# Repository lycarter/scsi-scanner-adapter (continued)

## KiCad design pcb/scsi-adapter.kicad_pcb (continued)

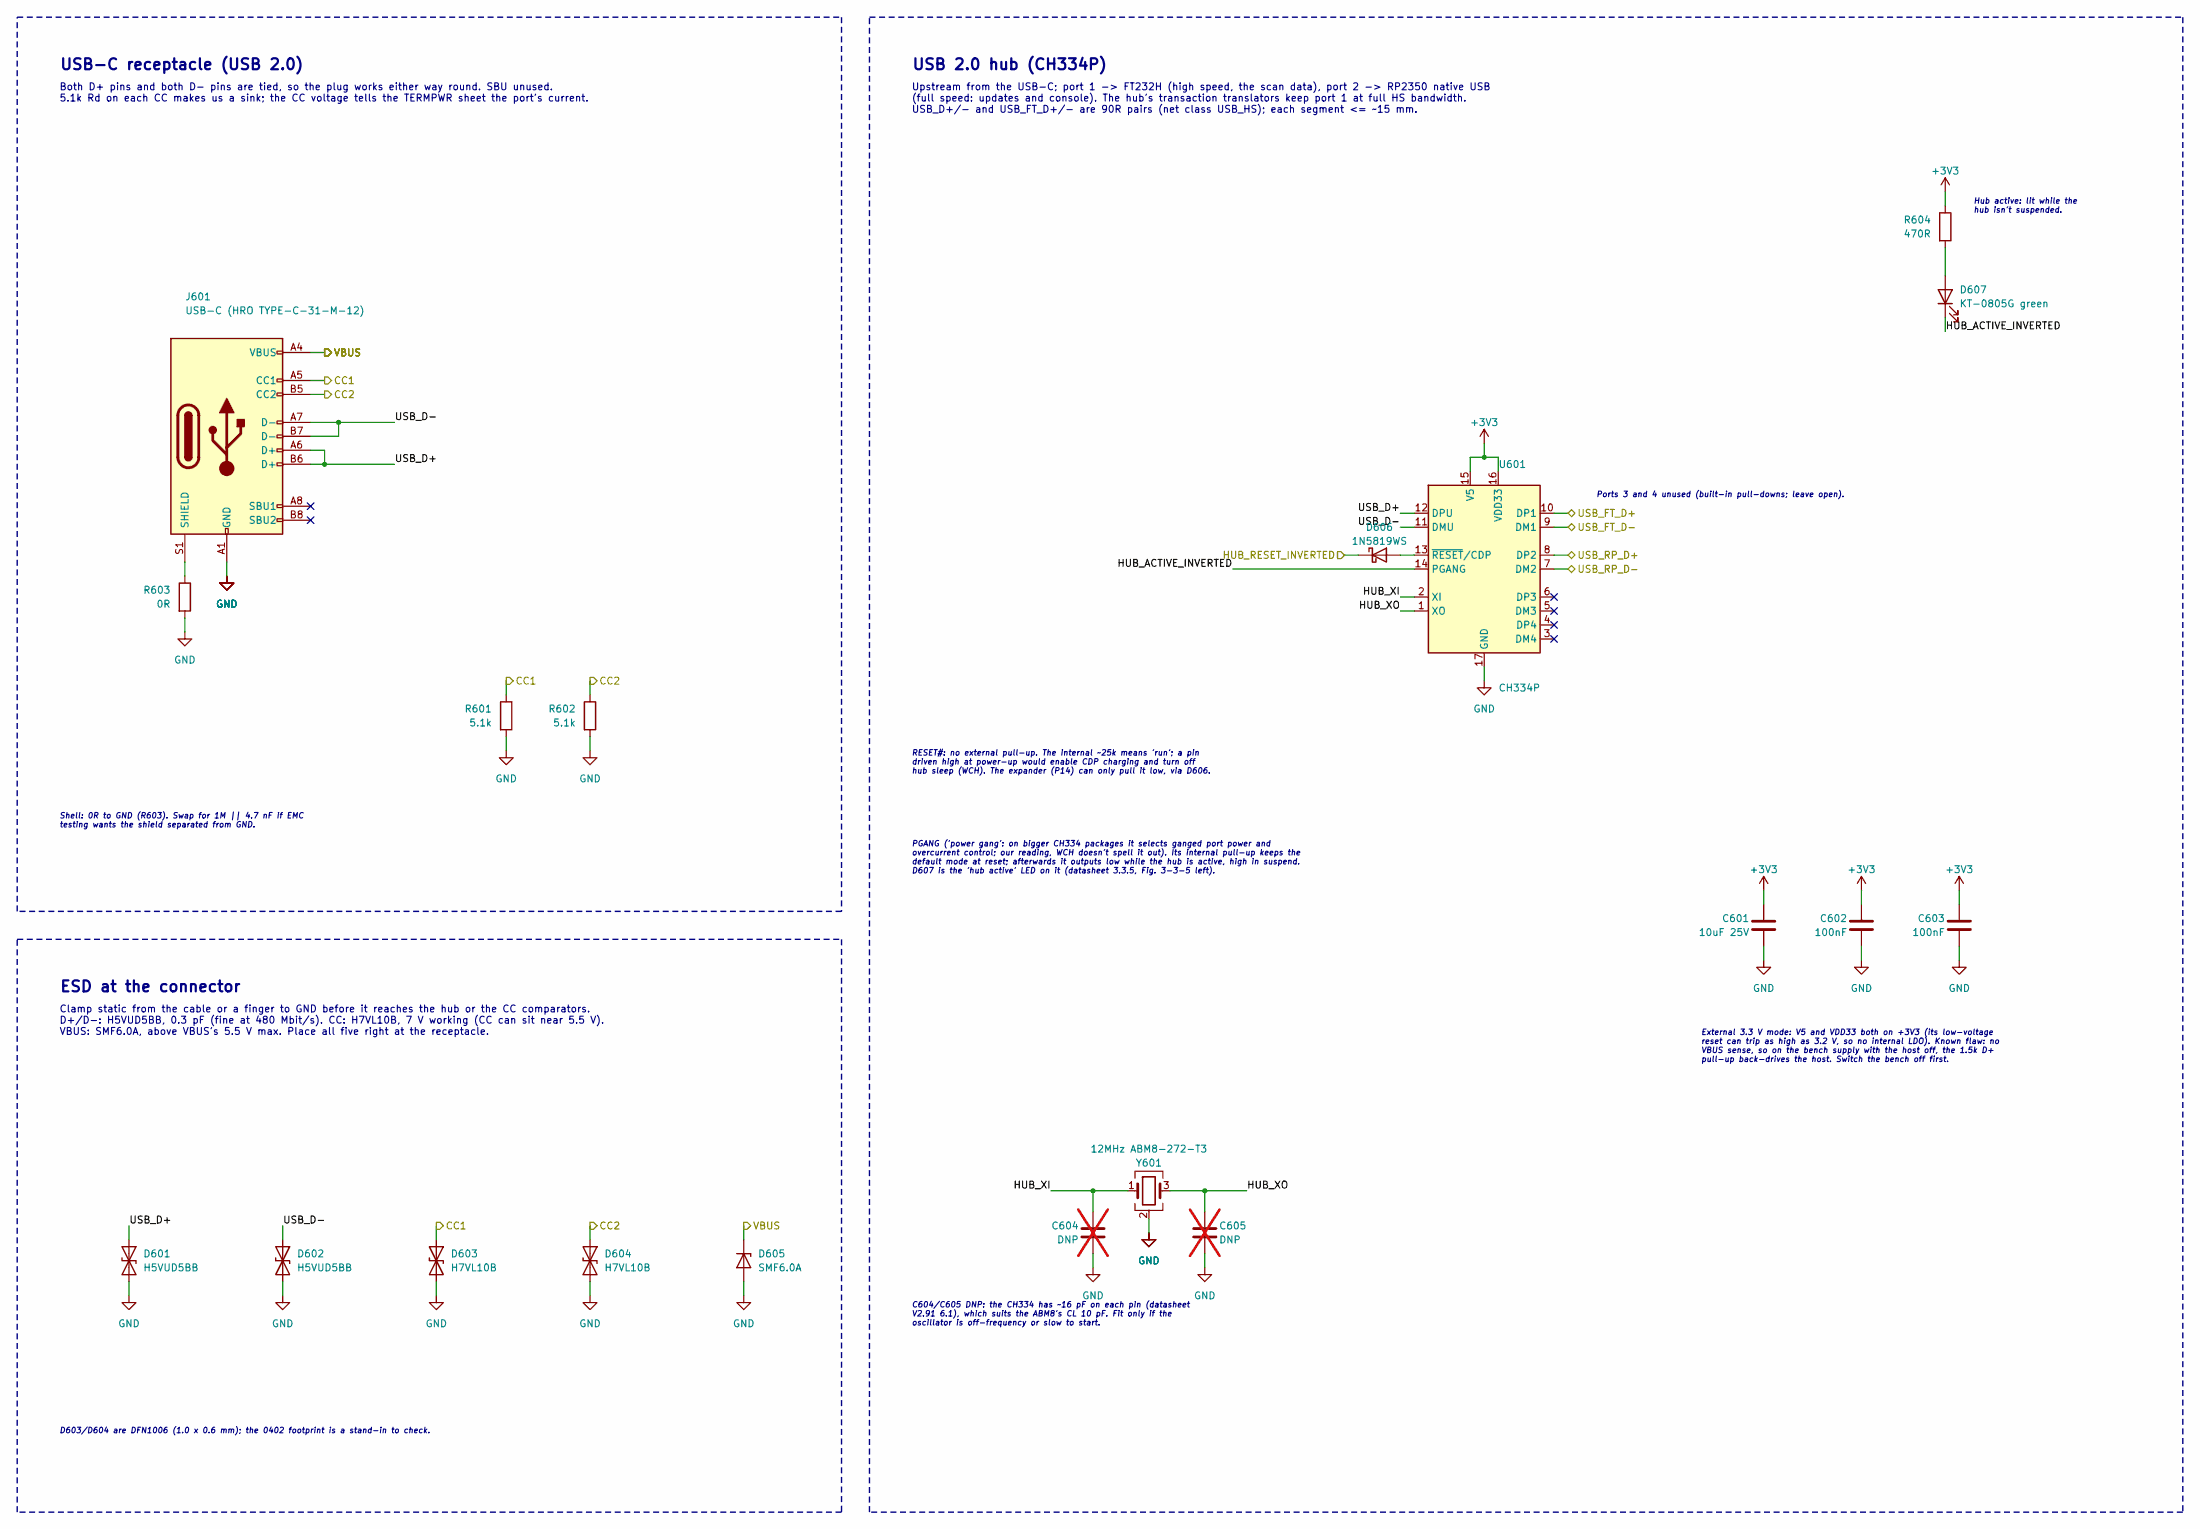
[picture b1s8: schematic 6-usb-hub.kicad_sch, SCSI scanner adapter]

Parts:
C601: 10uF 25V; C_0805_2012Metric; LCSC C15850
C602, C603: 100nF; C_0402_1005Metric; LCSC C307331
C604, C605: DNP; C_0402_1005Metric; not fitted
D601, D602: H5VUD5BB; D_SOD-523; LCSC C20615820
D603, D604: H7VL10B; D_0402_1005Metric; LCSC C20615787
D605: SMF6.0A; D_SOD-123F; LCSC C19077499
D606: 1N5819WS; D_SOD-323; LCSC C191023
D607: KT-0805G green; LED_0805_2012Metric; LCSC C2297
J601: USB-C (HRO TYPE-C-31-M-12); USB_C_Receptacle_HRO_TYPE-C-31-M-12
R601, R602: 5.1k; R_0402_1005Metric; LCSC C25905
R603: 0R; R_0402_1005Metric; LCSC C17168
R604: 470R; R_0402_1005Metric; LCSC C25117
U601: CH334P; QFN-16-1EP_3x3mm_P0.5mm_EP1.75x1.75mm; LCSC C5373042
Y601: 12MHz ABM8-272-T3; Crystal_SMD_3225-4Pin_3.2x2.5mm; LCSC C20625731

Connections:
+3V3: C601.1, C602.1, C603.1, R604.1, U601.15 (V5), U601.16 (VDD33); also elsewhere on the board
/CC1: D603.1 (A1), J601.A5 (CC1), R601.1; also elsewhere on the board
/CC2: D604.1 (A1), J601.B5 (CC2), R602.1; also elsewhere on the board
/HUB_RESET_INVERTED: D606.1 (K); also elsewhere on the board
/USB_FT_D+: U601.10 (DP1); also elsewhere on the board
/USB_FT_D-: U601.9 (DM1); also elsewhere on the board
/USB_RP_D+: U601.8 (DP2); also elsewhere on the board
/USB_RP_D-: U601.7 (DM2); also elsewhere on the board
/VBUS: D605.1 (K), J601.A4 (VBUS), J601.A9 (VBUS), J601.B4 (VBUS), J601.B9 (VBUS); also elsewhere on the board
/usb-hub/HUB_ACTIVE_INVERTED: D607.1 (K), U601.14 (PGANG)
/usb-hub/HUB_XI: C604.1, U601.2 (XI), Y601.1
/usb-hub/HUB_XO: C605.1, U601.1 (XO), Y601.3
/usb-hub/USB_D+: D601.1 (A1), J601.A6 (D+), J601.B6 (D+), U601.12 (DPU)
/usb-hub/USB_D-: D602.1 (A1), J601.A7 (D-), J601.B7 (D-), U601.11 (DMU)
GND: C601.2, C602.2, C603.2, C604.2, C605.2, D601.2 (A2), D602.2 (A2), D603.2 (A2), D604.2 (A2), D605.2 (A), J601.A1 (GND), J601.A12 (GND), J601.B1 (GND), J601.B12 (GND), R601.2, R602.2, R603.2, U601.17 (GND), Y601.2 (G), Y601.4 (G); also elsewhere on the board
unnamed: D606.2 (A), U601.13 (~RESET/CDP)
unnamed: D607.2 (A), R604.2
unnamed: J601.S1 (SHIELD), R603.1

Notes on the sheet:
PGANG ('power gang': on bigger CH334 packages it selects ganged port power and overcurrent control; our reading, WCH doesn't spell it out). Its internal pull-up keeps the default mode at reset; afterwards it outputs low while the hub is active, high in suspend. D607 is the 'hub active' LED on it (d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
C604/C605 DNP: the CH334 has ~16 pF on each pin (datasheet V2.91 6.1), which suits the ABM8's CL 10 pF. Fit only if the oscillator is off-frequency or slow to start.
RESET#: no external pull-up. The internal ~25k means 'run'; a pin driven high at power-up would enable CDP charging and turn off hub sleep (WCH). The expander (P14) can only pull it low, via D606.
ESD at the connector
Clamp static from the cable or a finger to GND before it reaches the hub or the CC comparators. D+/D-: H5VUD5BB, 0.3 pF (fine at 480 Mbit/s). CC: H7VL10B, 7 V working (CC can sit near 5.5 V). VBUS: SMF6.0A, above VBUS's 5.5 V max. Place all five right at the receptacle.
Shell: 0R to GND (R603). Swap for 1M || 4.7 nF if EMC testing wants the shield separated from GND.
External 3.3 V mode: V5 and VDD33 both on +3V3 (its low-voltage reset can trip as high as 3.2 V, so no internal LDO). Known flaw: no VBUS sense, so on the bench supply with the host off, the 1.5k D+ pull-up back-drives the host. Switch the bench off first.
Upstream from the USB-C; port 1 -> FT232H (high speed, the scan data), port 2 -> RP2350 native USB (full speed: updates and console). The hub's transaction translators keep port 1 at full HS bandwidth. USB_D+/- and USB_FT_D+/- are 90R pairs (net class USB_HS); each segment <= ~15 mm.
USB-C receptacle (USB 2.0)
Both D+ pins and both D- pins are tied, so the plug works either way round. SBU unused. 5.1k Rd on each CC makes us a sink; the CC voltage tells the TERMPWR sheet the port's current.
D603/D604 are DFN1006 (1.0 x 0.6 mm); the 0402 footprint is a stand-in to check.
USB 2.0 hub (CH334P)
Hub active: lit while the hub isn't suspended.
Ports 3 and 4 unused (built-in pull-downs; leave open).

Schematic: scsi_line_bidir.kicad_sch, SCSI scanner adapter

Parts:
C901: 22pF C0G; C_0402_1005Metric; LCSC C1555; not fitted
C902: 100nF 50V; C_0402_1005Metric; LCSC C307331
Q901: FDV301N; SOT-23; LCSC C15310
R901, R903: 100R; R_0402_1005Metric; LCSC C25076
R902: 4.7k; R_0402_1005Metric; LCSC C25900
U901: 74LVC1G17GW; SOT-353_SC-70-5; LCSC C426705

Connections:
+3V3: C902.1, U901.5 (VCC); also elsewhere on the board
/DB0_GATE: R901.1; also elsewhere on the board
/DB0_RX: R903.1, U901.4; also elsewhere on the board
/scsi/DB0_LOGIC_ANALYZER: R903.2; also elsewhere on the board
/scsi/~DB0: Q901.3 (D), U901.2; also elsewhere on the board
GND: C901.2, C902.2, Q901.2 (S), R902.2, U901.3 (GND); also elsewhere on the board
unnamed: C901.1, Q901.1 (G), R901.2, R902.1

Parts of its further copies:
C1001, C1101, C1201, C1301, C1401, C1501, C1601, C1701, C1801, C1901, C2001, C2101, C2301: 22pF C0G; C_0402_1005Metric; LCSC C1555; not fitted
C1002, C1102, C1202, C1302, C1402, C1502, C1602, C1702, C1802, C1902, C2002, C2102, C2302: 100nF 50V; C_0402_1005Metric; LCSC C307331
Q1001, Q1101, Q1201, Q1301, Q1401, Q1501, Q1601, Q1701, Q1801, Q1901, Q2001, Q2101, Q2301: FDV301N; SOT-23; LCSC C15310
R1001, R1003, R1101, R1103, R1201, R1203, R1301, R1303, R1401, R1403, R1501, R1503, R1601, R1603, R1701, R1703, R1801, R1803, R1901, R1903, R2001, R2003, R2101, R2103, R2301, R2303: 100R; R_0402_1005Metric; LCSC C25076
R1002, R1102, R1202, R1302, R1402, R1502, R1602, R1702, R1802, R1902, R2002, R2102, R2302: 4.7k; R_0402_1005Metric; LCSC C25900
U1001, U1101, U1201, U1301, U1401, U1501, U1601, U1701, U1801, U1901, U2001, U2101, U2301: 74LVC1G17GW; SOT-353_SC-70-5; LCSC C426705

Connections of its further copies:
+3V3: C1002.1, C1102.1, C1202.1, C1302.1, C1402.1, C1502.1, C1602.1, C1702.1, C1802.1, C1902.1, C2002.1, C2102.1, C2302.1, U1001.5 (VCC), U1101.5 (VCC), U1201.5 (VCC), U1301.5 (VCC), U1401.5 (VCC), U1501.5 (VCC), U1601.5 (VCC), U1701.5 (VCC), U1801.5 (VCC), U1901.5 (VCC), U2001.5 (VCC), U2101.5 (VCC), U2301.5 (VCC); also elsewhere on the board
/ACK_GATE: R2001.1; also elsewhere on the board
/ACK_RX: R2003.1, U2001.4; also elsewhere on the board
/ATN_GATE: R1801.1; also elsewhere on the board
/ATN_RX: R1803.1, U1801.4; also elsewhere on the board
/BSY_GATE: R1901.1; also elsewhere on the board
/BSY_RX: R1903.1, U1901.4; also elsewhere on the board
/DB1_GATE: R1001.1; also elsewhere on the board
/DB1_RX: R1003.1, U1001.4; also elsewhere on the board
/DB2_GATE: R1101.1; also elsewhere on the board
/DB2_RX: R1103.1, U1101.4; also elsewhere on the board
/DB3_GATE: R1201.1; also elsewhere on the board
/DB3_RX: R1203.1, U1201.4; also elsewhere on the board
/DB4_GATE: R1301.1; also elsewhere on the board
/DB4_RX: R1303.1, U1301.4; also elsewhere on the board
/DB5_GATE: R1401.1; also elsewhere on the board
/DB5_RX: R1403.1, U1401.4; also elsewhere on the board
/DB6_GATE: R1501.1; also elsewhere on the board
/DB6_RX: R1503.1, U1501.4; also elsewhere on the board
/DB7_GATE: R1601.1; also elsewhere on the board
/DB7_RX: R1603.1, U1601.4; also elsewhere on the board
/DBP_GATE: R1701.1; also elsewhere on the board
/DBP_RX: R1703.1, U1701.4; also elsewhere on the board
/RST_GATE: R2101.1; also elsewhere on the board
/RST_RX: R2103.1, U2101.4; also elsewhere on the board
/SEL_GATE: R2301.1; also elsewhere on the board
/SEL_RX: R2303.1, U2301.4; also elsewhere on the board
/scsi/ACK_LOGIC_ANALYZER: R2003.2; also elsewhere on the board
/scsi/ATN_LOGIC_ANALYZER: R1803.2; also elsewhere on the board
/scsi/BSY_LOGIC_ANALYZER: R1903.2; also elsewhere on the board
/scsi/DB1_LOGIC_ANALYZER: R1003.2; also elsewhere on the board
/scsi/DB2_LOGIC_ANALYZER: R1103.2; also elsewhere on the board
/scsi/DB3_LOGIC_ANALYZER: R1203.2; also elsewhere on the board
/scsi/DB4_LOGIC_ANALYZER: R1303.2; also elsewhere on the board
/scsi/DB5_LOGIC_ANALYZER: R1403.2; also elsewhere on the board
/scsi/DB6_LOGIC_ANALYZER: R1503.2; also elsewhere on the board
/scsi/DB7_LOGIC_ANALYZER: R1603.2; also elsewhere on the board
/scsi/DBP_LOGIC_ANALYZER: R1703.2; also elsewhere on the board
/scsi/RST_LOGIC_ANALYZER: R2103.2; also elsewhere on the board
/scsi/SEL_LOGIC_ANALYZER: R2303.2; also elsewhere on the board
/scsi/~ACK: Q2001.3 (D), U2001.2; also elsewhere on the board
/scsi/~ATN: Q1801.3 (D), U1801.2; also elsewhere on the board
/scsi/~BSY: Q1901.3 (D), U1901.2; also elsewhere on the board
/scsi/~DB1: Q1001.3 (D), U1001.2; also elsewhere on the board
/scsi/~DB2: Q1101.3 (D), U1101.2; also elsewhere on the board
/scsi/~DB3: Q1201.3 (D), U1201.2; also elsewhere on the board
/scsi/~DB4: Q1301.3 (D), U1301.2; also elsewhere on the board
/scsi/~DB5: Q1401.3 (D), U1401.2; also elsewhere on the board
/scsi/~DB6: Q1501.3 (D), U1501.2; also elsewhere on the board
/scsi/~DB7: Q1601.3 (D), U1601.2; also elsewhere on the board
/scsi/~DBP: Q1701.3 (D), U1701.2; also elsewhere on the board
/scsi/~RST: Q2101.3 (D), U2101.2; also elsewhere on the board
/scsi/~SEL: Q2301.3 (D), U2301.2; also elsewhere on the board
GND: C1001.2, C1002.2, C1101.2, C1102.2, C1201.2, C1202.2, C1301.2, C1302.2, C1401.2, C1402.2, C1501.2, C1502.2, C1601.2, C1602.2, C1701.2, C1702.2, C1801.2, C1802.2, C1901.2, C1902.2, C2001.2, C2002.2, C2101.2, C2102.2, C2301.2, C2302.2, Q1001.2 (S), Q1101.2 (S), Q1201.2 (S), Q1301.2 (S), Q1401.2 (S), Q1501.2 (S), Q1601.2 (S), Q1701.2 (S), Q1801.2 (S), Q1901.2 (S), Q2001.2 (S), Q2101.2 (S), Q2301.2 (S), R1002.2, R1102.2, R1202.2, R1302.2, R1402.2, R1502.2, R1602.2, R1702.2, R1802.2, R1902.2, R2002.2, R2102.2, R2302.2, U1001.3 (GND), U1101.3 (GND), U1201.3 (GND), U1301.3 (GND), U1401.3 (GND), U1501.3 (GND), U1601.3 (GND), U1701.3 (GND), U1801.3 (GND), U1901.3 (GND), U2001.3 (GND), U2101.3 (GND), U2301.3 (GND); also elsewhere on the board
unnamed: C1001.1, Q1001.1 (G), R1001.2, R1002.1
unnamed: C1101.1, Q1101.1 (G), R1101.2, R1102.1
unnamed: C1201.1, Q1201.1 (G), R1201.2, R1202.1
unnamed: C1301.1, Q1301.1 (G), R1301.2, R1302.1
unnamed: C1401.1, Q1401.1 (G), R1401.2, R1402.1
unnamed: C1501.1, Q1501.1 (G), R1501.2, R1502.1
unnamed: C1601.1, Q1601.1 (G), R1601.2, R1602.1
unnamed: C1701.1, Q1701.1 (G), R1701.2, R1702.1
unnamed: C1801.1, Q1801.1 (G), R1801.2, R1802.1
unnamed: C1901.1, Q1901.1 (G), R1901.2, R1902.1
unnamed: C2001.1, Q2001.1 (G), R2001.2, R2002.1
unnamed: C2101.1, Q2101.1 (G), R2101.2, R2102.1
unnamed: C2301.1, Q2301.1 (G), R2301.2, R2302.1

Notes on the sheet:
SCSI line with driver
C1 DNP: fit only if a rising bus edge, coupled through the FET's gate-drain capacitance, makes a visible dip or step (board off, G4 driving the bus).
x14: DB0-7, DBP, ATN, BSY, ACK, RST, SEL (pages 9-21 except MSG). References: page x 100 + n. Driver: GATE high = line asserted (Q1 pulls it to ~0.2 V). Receiver: RX low = line asserted (the RP2350 pad inverts it). Place this cluster on its own bus trace next to the connector.
R3 feeds the logic-analyzer header; the RP2350 input takes RX straight from U1.

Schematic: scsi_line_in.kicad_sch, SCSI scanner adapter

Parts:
C2202: 100nF 50V; C_0402_1005Metric; LCSC C307331
R2203: 100R; R_0402_1005Metric; LCSC C25076
U2201: 74LVC1G17GW; SOT-353_SC-70-5; LCSC C426705

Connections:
+3V3: C2202.1, U2201.5 (VCC); also elsewhere on the board
/MSG_RX: R2203.1, U2201.4; also elsewhere on the board
/scsi/MSG_LOGIC_ANALYZER: R2203.2; also elsewhere on the board
/scsi/~MSG: U2201.2; also elsewhere on the board
GND: C2202.2, U2201.3 (GND); also elsewhere on the board

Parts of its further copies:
C2402, C2502, C2602: 100nF 50V; C_0402_1005Metric; LCSC C307331
R2403, R2503, R2603: 100R; R_0402_1005Metric; LCSC C25076
U2401, U2501, U2601: 74LVC1G17GW; SOT-353_SC-70-5; LCSC C426705

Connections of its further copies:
+3V3: C2402.1, C2502.1, C2602.1, U2401.5 (VCC), U2501.5 (VCC), U2601.5 (VCC); also elsewhere on the board
/CD_RX: R2403.1, U2401.4; also elsewhere on the board
/IO_RX: R2603.1, U2601.4; also elsewhere on the board
/REQ_RX: R2503.1, U2501.4; also elsewhere on the board
/scsi/CD_LOGIC_ANALYZER: R2403.2; also elsewhere on the board
/scsi/IO_LOGIC_ANALYZER: R2603.2; also elsewhere on the board
/scsi/REQ_LOGIC_ANALYZER: R2503.2; also elsewhere on the board
/scsi/~CD: U2401.2; also elsewhere on the board
/scsi/~IO: U2601.2; also elsewhere on the board
/scsi/~REQ: U2501.2; also elsewhere on the board
GND: C2402.2, C2502.2, C2602.2, U2401.3 (GND), U2501.3 (GND), U2601.3 (GND); also elsewhere on the board

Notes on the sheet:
x4: MSG, C/D, REQ, I/O. The initiator never drives these (SCSI-2 Table 6: target-only). RX low = line asserted (the RP2350 pad inverts it). References: page x 100 + n.
SCSI line, receive only
R3 feeds the logic-analyzer header; the RP2350 input takes RX straight from U1.

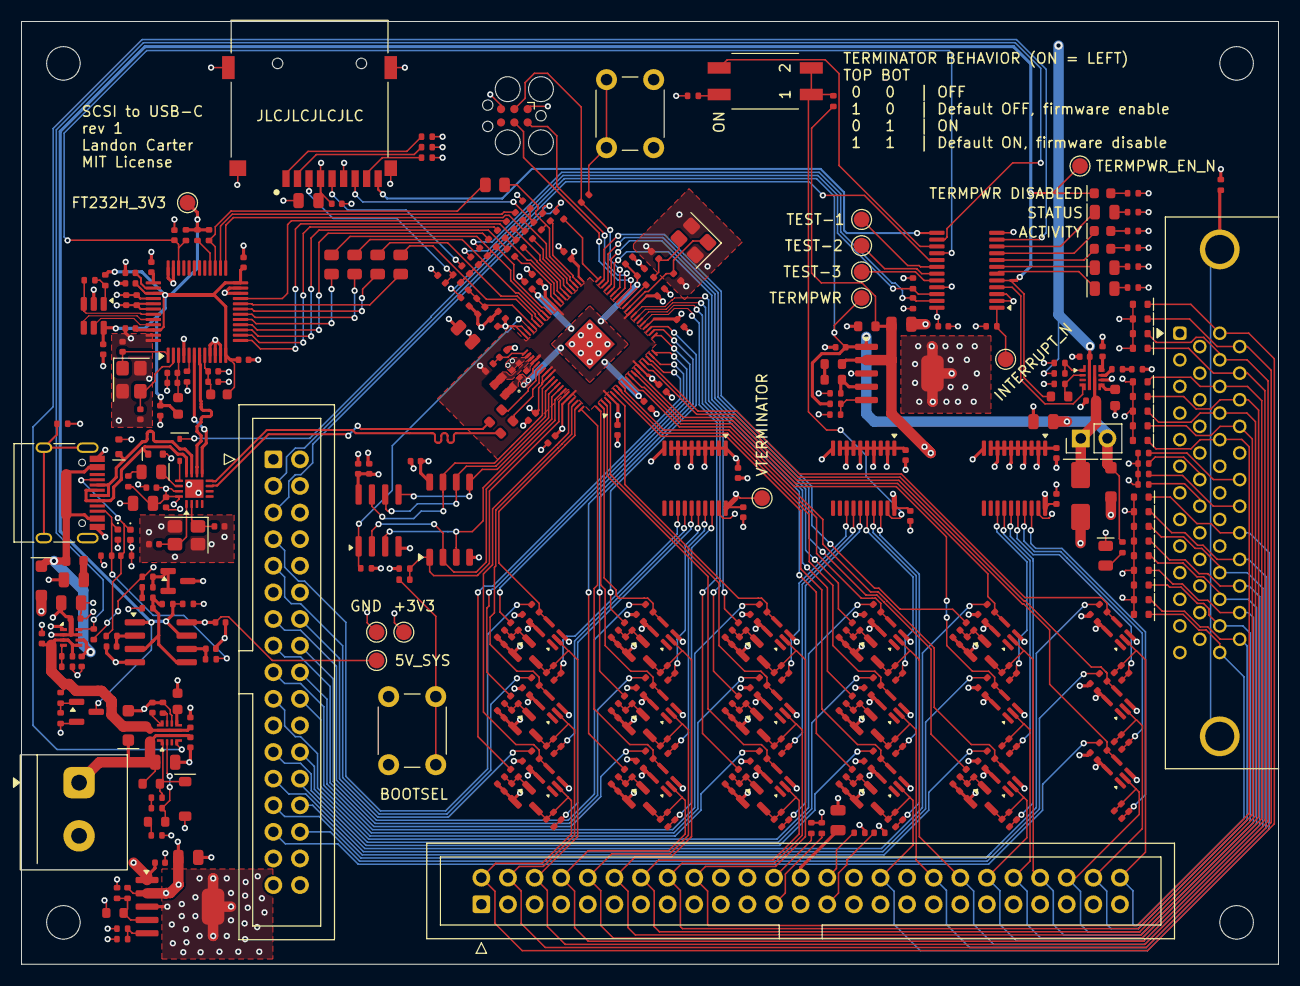
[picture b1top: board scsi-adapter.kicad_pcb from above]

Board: 4 copper layers, 120.0 x 90.0 mm, 412 parts (0 on the bottom side), 254 nets.

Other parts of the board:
5V_SYS: +5V_SYS; TestPoint_Pad_D1.5mm
+3V3: +3V3; TestPoint_Pad_D1.5mm
FT232H_3V3: FT232H_3V3; TestPoint_Pad_D1.5mm
GND: GND; TestPoint_Pad_D1.5mm
H1, H2, H3, H4: M3; MountingHole_3.2mm_M3
INTERRUPT_N: INT; TestPoint_Pad_D1.5mm
TERMPWR: TERMPWR; TestPoint_Pad_D1.5mm
TERMPWR_EN_N: TP_EN; TestPoint_Pad_D1.5mm
TEST-1: P15; TestPoint_Pad_D1.5mm
TEST-2: P16; TestPoint_Pad_D1.5mm
TEST-3: P17; TestPoint_Pad_D1.5mm
VTERMINATOR: VTERM; TestPoint_Pad_D1.5mm

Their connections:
+3V3: +3V3.1; also elsewhere on the board
+5V_SYS: 5V_SYS.1; also elsewhere on the board
/TERMPWR_EN_INVERTED: TERMPWR_EN_N.1; also elsewhere on the board
/io/EXPANDER_INTERRUPT_INVERTED: INTERRUPT_N.1; also elsewhere on the board
/io/EXPANDER_P15: TEST-1.1; also elsewhere on the board
/io/EXPANDER_P16: TEST-2.1; also elsewhere on the board
/io/EXPANDER_P17: TEST-3.1; also elsewhere on the board
FT232H_3V3: FT232H_3V3.1; also elsewhere on the board
GND: GND.1; also elsewhere on the board
TERMPWR: TERMPWR.1; also elsewhere on the board
VTERMINATOR: VTERMINATOR.1; also elsewhere on the board

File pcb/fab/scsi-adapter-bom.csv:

Comment,Designator,Footprint,LCSC Part #
1uF 50V X7R,C101,C_0805_2012Metric,C28323
100nF 50V,"C102,C108,C203,C206,C301,C302,C303,C304,C305,C306,C406,C407,C408,C409,C410,C411,C412,C413,C414,C415,C416,C417,C418,C421,C422,C424,C501,C503,C602,C603,C702,C704,C705,C706,C707,C708,C710,C712,C713,C714,C902,C1002,C1102,C1202,C1302,C1402,C1502,C1602,C1702,C1802,C1902,C2002,C2102,C2202,C2302,C2402,C2502,C2602",C_0402_1005Metric,C307331
2.2nF,"C103,C204",C_0603_1608Metric,C1604
1uF 25V,"C105,C106,C110,C112,C114,C201,C202,C207,C423",C_0402_1005Metric,C52923
4.7uF 25V,"C107,C307,C308",C_0805_2012Metric,C1779
22uF 25V,C109,C_0805_2012Metric,C45783
10uF 25V,"C111,C113,C405,C502,C601",C_0805_2012Metric,C15850
4.7uF 10V,"C401,C402,C403,C404,C701,C703",C_0402_1005Metric,C23733
15pF,"C419,C420,C715,C716",C_0402_1005Metric,C1548
10nF,C717,C_0402_1005Metric,C15195
BZT52C5V6,D102,D_SOD-123,C19077402
KT-0603R red,"D201,D502,D503",LED_0603_1608Metric,C2286
KT-0805Y yellow,"D202,D501,D504",LED_0805_2012Metric,C2296
SMF6.0A,"D204,D605",D_SOD-123F,C19077499
H5VUD5BB,"D301,D302,D303,D304,D305,D306,D307,D308,D309,D310,D311,D312,D313,D314,D315,D316,D317,D318,D601,D602",D_SOD-523,C20615820
KT-0805G green,"D505,D607",LED_0805_2012Metric,C2297
H7VL10B,"D603,D604",D_0402_1005Metric,C20615787
1N5819WS,D606,D_SOD-323,C191023
600R@100MHz,"FB701,FB702",L_0603_1608Metric,C1002
TF PUSH,J501,microSD_SHOUHAN_TF-PUSH_PushPush_CardDetect,C393941
3.3uH,L401,L_Abracon_AOTA-B201610_2.0x1.6mm_Polarized,C42411119
2N7002,Q201,SOT-23,C8545
FDV301N,"Q901,Q1001,Q1101,Q1201,Q1301,Q1401,Q1501,Q1601,Q1701,Q1801,Q1901,Q2001,Q2101,Q2301",SOT-23,C15310
0R,"R1,R2,R3,R4,R337,R338,R339,R340,R343,R418,R420,R422,R424,R426,R603",R_0402_1005Metric,C17168
510k,R101,R_0603_1608Metric,C23192
33k,"R102,R114,R120",R_0402_1005Metric,C25779
10k,"R103,R105,R109,R201,R202,R204,R208,R210,R212,R341,R503,R506,R507,R508,R509,R510,R702,R703,R705,R706",R_0402_1005Metric,C25744
150k,"R104,R115",R_0603_1608Metric,C22807
1.5k,R106,R_0402_1005Metric,C25867
51k,"R107,R213",R_0402_1005Metric,C25794
20k,"R108,R111,R116,R214",R_0402_1005Metric,C25765
1R,R110,R_0603_1608Metric,C22936
15k,"R112,R117",R_0402_1005Metric,C25756
47k,"R113,R216",R_0402_1005Metric,C25792
39k,R118,R_0603_1608Metric,C23153
5.6k,R119,R_0603_1608Metric,C23189
270R,R121,R_0603_1608Metric,C22966
470R,"R203,R513,R604",R_0402_1005Metric,C25117
3.3k,"R205,R403",R_0402_1005Metric,C25890
4.7k,"R206,R501,R502,R902,R1002,R1102,R1202,R1302,R1402,R1502,R1602,R1702,R1802,R1902,R2002,R2102,R2302",R_0402_1005Metric,C25900
1M,R207,R_0402_1005Metric,C26083
1k,"R209,R342,R402,R405,R406,R504,R505,R511,R512",R_0402_1005Metric,C11702
100k,"R211,R428,R429",R_0402_1005Metric,C25741
56k,R215,R_0603_1608Metric,C23206
2.2k,"R217,R704",R_0402_1005Metric,C25879
510R,R218,R_0402_1005Metric,C25123
220R,"R301,R302,R303,R304,R305,R306,R307,R308,R309,R310,R311,R312,R313,R314,R315,R316,R317,R318,R319,R320,R321,R322,R323,R324,R325,R326,R327,R328,R329,R330,R331,R332,R333,R334,R335,R336",R_0402_1005Metric,C25091
33R,"R401,R407,R408,R409,R410,R411,R412,R413",R_0402_1005Metric,C25105
100R,"R414,R415,R901,R903,R1001,R1003,R1101,R1103,R1201,R1203,R1301,R1303,R1401,R1403,R1501,R1503,R1601,R1603,R1701,R1703,R1801,R1803,R1901,R1903,R2001,R2003,R2101,R2103,R2203,R2301,R2303,R2403,R2503,R2603",R_0402_1005Metric,C25076
27R,"R416,R417",R_0603_1608Metric,C25190
5.1k,"R601,R602",R_0402_1005Metric,C25905
12k 1%,R701,R_0402_1005Metric,C25752
DIP 2-pos,SW301,SW_DIP_SPSTx02_Slide_SHOUHAN_2.54-2P-TPGT_W8.8mm_P2.54mm,C6331180
TPS259470ARPWR,"U101,U201",Texas_RPW0010A_VQFN-HR-10_2x2mm_P0.45mm,C3662799
TPS2116DRLR,U102,SOT-583-8,C3235557
TPS73701DCQR,"U103,U104",SOT-223-6,C56848
LM393DR2G,U202,SOIC-8_3.9x4.9mm_P1.27mm,C7955
CJ431,U203,SOT-23,C3113
SN74LVTH245APWR,"U301,U302,U303",TSSOP-20_4.4x6.5mm_P0.65mm,C2652121
RP2350B,U401,QFN-80-1EP_10x10mm_P0.4mm_EP3.4x3.4mm,C42415655
W25Q128JVSIQ,U402,SOIC-8_5.3x5.3mm_P1.27mm,C97521
APS6404L-3SQR-SN,U403,SOIC-8_3.9x4.9mm_P1.27mm,C5333729
TCA9555PWR,U501,TSSOP-24_4.4x7.8mm_P0.65mm,C465732
CH334P,U601,QFN-16-1EP_3x3mm_P0.5mm_EP1.75x1.75mm,C5373042
FT232HL,U701,LQFP-48_7x7mm_P0.5mm,C51997
93LC56BT-I/OT,U702,SOT-23-6,C190271
74LVC1G17GW,"U901,U1001,U1101,U1201,U1301,U1401,U1501,U1601,U1701,U1801,U1901,U2001,U2101,U2201,U2301,U2401,U2501,U2601",SOT-353_SC-70-5,C426705
12MHz ABM8-272-T3,"Y401,Y601,Y701",Crystal_SMD_3225-4Pin_3.2x2.5mm,C20625731

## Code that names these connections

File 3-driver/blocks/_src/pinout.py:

# Page 5: RP2350B pin map. Rendered into ../5-rp2350-pinout.md by build.py.
# Physical pins: RP2350 datasheet §1.2.1, Figure 3 (QFN-80, top view).
from canvas import Diagram
D = Diagram()

# Package pin -> pad name, counter-clockwise from pin 1 (datasheet Figure 3).
PADS = {n: f"GPIO{g}" for n, g in zip(range(1, 5), range(4, 8))}
PADS.update({5: 'IOVDD', 6: 'GPIO8', 7: 'GPIO9', 8: 'GPIO10', 9: 'GPIO11', 10: 'DVDD',
             11: 'GPIO12', 12: 'GPIO13', 13: 'GPIO14', 14: 'GPIO15', 15: 'IOVDD',
             16: 'GPIO16', 17: 'GPIO17', 18: 'GPIO18', 19: 'GPIO19', 20: 'GPIO20',
             21: 'GPIO21', 22: 'GPIO22', 23: 'GPIO23', 24: 'IOVDD', 25: 'GPIO24',
             26: 'GPIO25', 27: 'GPIO26', 28: 'GPIO27', 29: 'IOVDD', 30: 'XIN', 31: 'XOUT',
             32: 'DVDD', 33: 'SWCLK', 34: 'SWDIO', 35: 'RUN', 36: 'GPIO28', 37: 'GPIO29',
             38: 'GPIO30', 39: 'GPIO31', 40: 'GPIO32',
             41: 'IOVDD', 42: 'GPIO33', 43: 'GPIO34', 44: 'GPIO35', 45: 'GPIO36',
             46: 'GPIO37', 47: 'GPIO38', 48: 'GPIO39', 49: 'GPIO40_ADC0', 50: 'IOVDD',
             51: 'DVDD', 52: 'GPIO41_ADC1', 53: 'GPIO42_ADC2', 54: 'GPIO43_ADC3',
             55: 'GPIO44_ADC4', 56: 'GPIO45_ADC5', 57: 'GPIO46_ADC6', 58: 'GPIO47_ADC7',
             59: 'ADC_AVDD', 60: 'IOVDD',
             61: 'VREG_AVDD', 62: 'VREG_PGND', 63: 'VREG_LX', 64: 'VREG_VIN', 65: 'VREG_FB',
             66: 'USB_DM', 67: 'USB_DP', 68: 'USB_OTP_VDD', 69: 'QSPI_IOVDD', 70: 'QSPI_SD3',
             71: 'QSPI_SCLK', 72: 'QSPI_SD0', 73: 'QSPI_SD2', 74: 'QSPI_SD1', 75: 'QSPI_SS',
             76: 'IOVDD', 77: 'GPIO0', 78: 'GPIO1', 79: 'GPIO2', 80: 'GPIO3'})

# What each GPIO carries (accepted 2026-09-25; review changes 2026-09-26: ATN on PIO0 out+9,
# GPIO 46 = TERMPWR ADC, CS1 pull-up 3.3k). Both SCSI blocks follow the SCSI-2 connector
# order (Table 2: DB0-7, DBP, ATN, BSY, ACK, RST, MSG, SEL, C/D, REQ, I/O). "in" = receiver output (INOVER: 1 = asserted),
# "gate" = FDV301N gate (1 = asserted).
DB = ['DB0', 'DB1', 'DB2', 'DB3', 'DB4', 'DB5', 'DB6', 'DB7', 'DBP']
GPIO = {}
for k, s in enumerate(DB):
    GPIO[k] = (f"{s} in", f"PIO0 in+{k}")
for k, s in enumerate(['ATN', 'BSY', 'ACK', 'RST', 'MSG', 'SEL', 'C/D', 'REQ', 'I/O'], start=9):
    GPIO[k] = (f"{s} in", f"PIO0 in+{k}")
for k, s in enumerate(DB):
    GPIO[18 + k] = (f"{s} gate", f"PIO0 out+{k}")
GPIO.update({
    27: ('ATN gate', 'PIO0 out+9'), 28: ('BSY gate', 'CPU'), 29: ('ACK gate', 'PIO0 side-set'),
    30: ('RST gate', 'CPU only'), 31: ('SEL gate', 'CPU'),
    32: ('FT MIOSIO0', 'PIO1; FIFO D0'), 33: ('FT MIOSIO1', 'PIO1; FIFO D1'),
    34: ('FT MIOSIO2', 'PIO1; FIFO D2'), 35: ('FT MIOSIO3', 'PIO1; FIFO D3'),
    # Fallback (NOTES "FT1248 fallback plan"): move the 0R links and these pins become FT232H
    # FIFO / 8-bit FT1248 lines. FT pin numbers are FT232H package pins (DS v2.0).
    36: ('I2C0 SDA', '0R >> FIFO D4 (FT 17)'), 37: ('I2C0 SCL', '0R >> FIFO D5 (FT 18)'),
    38: ('SD CLK', '0R >> FIFO D6 (FT 19)'), 39: ('SD CMD', '0R >> FIFO D7 (FT 20)'),
    40: ('SD D0', '0R >> FIFO WR# (FT 27)'),
    41: ('FT SCLK', 'PIO1; FIFO RXF#'), 42: ('FT SS_n', 'PIO1; FIFO TXE#'),
    43: ('FT MISO', 'PIO1; FIFO RD#'),
    44: ('LA marker 0', 'CPU'), 45: ('LA marker 1', 'CPU'), 46: ('TERMPWR ADC', 'ADC6, 100k/100k'),
    47: ('PSRAM CS1', 'QMI, 3.3k up'),
})
OTHER = {
    'IOVDD': '3.3 V', 'DVDD': '1.1 V core', 'ADC_AVDD': '3.3 V', 'USB_OTP_VDD': '3.3 V',
    'QSPI_IOVDD': '3.3 V', 'XIN': '12 MHz crystal', 'XOUT': '12 MHz crystal',
    'SWCLK': 'TC2030 pad 4', 'SWDIO': 'TC2030 pad 2', 'RUN': 'RUN btn; TC2030 pad 3',
    'VREG_AVDD': 'core reg (33R+4u7)', 'VREG_PGND': 'core reg GND', 'VREG_LX': 'core reg L',
    'VREG_VIN': 'core reg 3.3 V in', 'VREG_FB': 'core reg -> DVDD',
    'USB_DM': 'hub port 2 D-', 'USB_DP': 'hub port 2 D+',
    'QSPI_SS': 'flash CS, BOOTSEL', 'QSPI_SCLK': 'flash + PSRAM',
    'QSPI_SD0': 'flash + PSRAM', 'QSPI_SD1': 'flash + PSRAM',
    'QSPI_SD2': 'flash + PSRAM', 'QSPI_SD3': 'flash + PSRAM',
}

pins = {}
for num, pad in PADS.items():
    if pad.startswith('GPIO'):
        g = int(pad[4:].split('_')[0])
        sig, owner = GPIO[g]
        pins[num] = (pad, f"{sig:<11} {owner}")
    else:
        pins[num] = (pad, OTHER[pad])

D.chip45('rp', 0, 0, 20, pins, name='RP2350B',
         inner=["RP2350B", "QFN-80, top view", "", "rotated 45 deg CCW:", "package top edge",
                "faces upper-left", "", "* = pin 1", "EP (81) = GND"])

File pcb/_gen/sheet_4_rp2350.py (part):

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SHEET_SYM = "09e6debe-d957-4263-8f90-e8efff15a584"          # the "rp2350" sheet symbol on the root

LINES = ["DB0", "DB1", "DB2", "DB3", "DB4", "DB5", "DB6", "DB7", "DBP", "ATN", "BSY", "ACK", "RST", "MSG",
         "SEL", "CD", "REQ", "IO"]                               # GPIO 0-17 = receiver outputs
GATES = ["DB0", "DB1", "DB2", "DB3", "DB4", "DB5", "DB6", "DB7", "DBP", "ATN", "BSY", "ACK", "RST", "SEL"]
# GPIO 32-46 order from the crossing-count solver (design_docs/3-driver/tools/ft1248_pinsolve.py, 2026-09-27)
FT1248 = {38: "FT232H_MIOSIO0", 39: "FT232H_MIOSIO1", 40: "FT232H_MIOSIO2", 41: "FT232H_MIOSIO3", 37: "FT232H_SCLK",
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           "Logic-analyzer marker series R"), "US": ("27R", "C25190", R0603, "Native USB series R")}
    rows = sorted(((s.pin_pos(upins, n, MX, MY, 0), n) for n in SERIES), key=lambda t: (t[0][2], t[0][1]))
    col = {}
    for (px, py, d), n in rows:                               # alternate columns down each run of pins
        prev = [k for k in col if k[0] == d and abs(k[1] - (py - G)) < 0.01]
        col[(d, py)] = 1 - col[prev[0]] if prev else 1         # start outside the neighbouring labels
        out, ref = SERIES[n]
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    s.power("GND", MX, bot + G, 270)
    s.intended[("U401", "62")] = s.intended[("U401", "81")] = "GND"
    s.note("Top pins: USB_OTP_VDD, ADC_AVDD, QSPI_IOVDD, IOVDD (x8) and\nVREG_VIN share +3V3; VREG_FB and DVDD (x3) "
           "are the 1.1 V core\nrail (DVDD_1V1), made by the on-chip regulator. Each supply\npin gets its own 100 nF "
           "(Decoupling box).", 167.64, 43.18)

    # ================= Core regulator =================
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    heading(s, "Core regulator (on-chip, 1.1 V)", 20.32, 20.32,
            "Guide 2.1 / datasheet 6.3.8. Layout: inductor orientation per Fig. 23, VREG_PGND and CIN\n"
            "straight to the exposed pad, and a ground cut-out under VREG_LX on layer 2 (Fig. 24).")
    s.part("Device:L", "L401", "3.3uH", 60.96, 50.8, {"1": "DVDD_1V1", "2": "VREG_LX"}, a=90,
           props=props("scsi-adapter:L_Abracon_AOTA-B201610_2.0x1.6mm_Polarized", "C42411119",
                       note="Abracon AOTA-B201610S3R3-101-T, polarity-marked: pad 1 = dot = DVDD (RP2350 Fig. 23)"),
           fields=((60.96, 46.99, ""), (60.96, 54.61, "")))
    s.note("Pin 1 = the part's dot = DVDD_1V1 (datasheet Fig. 23,\nPico 2 layout). Check JLC's placement preview.", 43.18, 58.42)
    s.pwr_flag("#FLG401", "DVDD_1V1", 81.28, 38.1)
    s.pwr_flag("#FLG402", "VREG_AVDD", 124.46, 38.1)
    s.note("PWR_FLAGs: DVDD_1V1 is fed through L401 and VREG_AVDD\nthrough R401, which ERC sees as passive parts.",
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          "+3V3", "GND", taps={0: "VREG_AVDD"})
    for i, (ref, net, note) in enumerate((("C402", "+3V3", "CIN at VREG_VIN (pin 64)"),
                                          ("C403", "DVDD_1V1", "COUT at VREG_FB/DVDD"),
                                          ("C404", "DVDD_1V1", "Second DVDD cap at pin 32 (bottom edge, away from LX)"))):
        x = 25.4 + i * 20.32
        # CIN/COUT use Raspberry Pi's wide 0402: their layout runs the VREG_LX pour between the pads
        fpn = "scsi-adapter:C_0402_1005Metric_Wide" if ref in ("C402", "C403") else C0402
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    s.part("Device:C", "C420", "15pF", 447.04, YY + 7.62, {"1": None, "2": "GND"},
           props=props(C0402, "C1548", note="Crystal load cap"),
           fields=((449.58, YY + 6.35, "left"), (449.58, YY + 8.89, "left")))
    s.part("Device:R", "R402", "1k", 455.93, YY, {"1": None, "2": "XOUT"}, a=90,
           props=props(R0402, "C11702", note="XOUT series R (guide 4)"), fields=((455.93, YY - 2.54, ""), (455.93, YY + 2.54, "")))
    for k in (("Y401", "1"), ("C419", "1")):
        s.intended[k] = "XIN"
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    # ================= TERMPWR sense =================
    s.rect(12.7, 306.07, 154.94, 406.4)
    heading(s, "TERMPWR sense (ADC6)", 20.32, 313.69,
            "0.5 x TERMPWR on GPIO 46: 0-5.6 V -> 0-2.8 V.\nDraws 26 uA from TERMPWR.")
    chain(43.18, 340.36, [("R428", "Device:R", "100k", props(R0402, "C25741", note="TERMPWR sense top"),
                           0, "1", "2", 3.81, False),
                          ("R429", "Device:R", "100k", props(R0402, "C25741", note="TERMPWR sense bottom"),
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
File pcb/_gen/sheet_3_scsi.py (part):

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# Header pin -> net. Originally DIN0-17 = the 18 lines in GPIO order and DIN18/19 = the markers; the signals
# were reshuffled during layout (2026-10) to suit the routing, so the map is now explicit. Every line and both
# markers are still present once; ground and unused pins did not move.
LA_PIN = {3: "LOGIC_ANALYZER_MARKER0", 5: "LOGIC_ANALYZER_MARKER1",
          7: "DB2", 9: "DB1", 13: "DB5", 15: "DB3", 17: "DB7", 19: "ACK", 23: "ATN", 25: "MSG", 27: "IO", 29: "CD",
          14: "DB0", 16: "DB4", 18: "DBP", 20: "DB6", 24: "BSY", 26: "SEL", 28: "RST", 30: "REQ"}
assert sorted(n for n in LA_PIN.values() if "MARKER" not in n) == sorted(n for n, _ in LINES)
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    s.part("Device:R", "R343", "0R", shx, shy + 6.35, {"1": None, "2": "GND"},
           props=props(R0402, "C17168", note="HD50 shell to GND (replace with 1M || 4.7nF if EMC asks)"))
    s.intended[("J302", "SH")] = s.intended[("R343", "1")] = "~hd50_shell"
    s.note("Pin 25 (HD50 13) is OPEN: a reversed ribbon puts TERMPWR on a\ndead pin, not on ground. "
           "IDC50 even pins 20, 22, 30, 34 are GROUND.", 20.32, 114.3)
    for i, (pin, net) in enumerate(sorted(RES.items())):
        x = 33.02 + i * 30.48
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        s.part("Device:R", f"R{1 + i}", "0R", 149.86 + i * 20.32, 135.89, {"1": net + "_hd50", "2": "GND"},
               props=props(R0402, "C17168", note="RESERVED line to ground (SCSI-2 5.4.4); remove if mid-chain"),
               fields="left")
    # TERMPWR bulk, one beside each connector's TERMPWR pin (2026-10-04 layout review: the rail had 2 x 1 uF,
    # both 38-51 mm from the connectors).
    for ref, x, where in (("C307", 228.6, "J301 pin 26"), ("C308", 246.38, "J302 pin 38")):
        s.part("Device:C", ref, "4.7uF 25V", x, 135.89, {"1": "TERMPWR", "2": "GND"},
               props=props("Capacitor_SMD:C_0805_2012Metric", "C1779", note=f"TERMPWR bulk: place at {where}"),
               fields="left")
    s.note("C307/C308: TERMPWR bulk, one beside each\nconnector's TERMPWR pin (J301.26, J302.38).", 205.74, 151.13)
    s.note("SCSI-2 5.4.4: RESERVED lines 'shall be connected to ground' in end devices, 'should be open'\n"
           "otherwise. We are an end device: all four fitted. Remove R337-R340 and R1-R4 if the board ever sits mid-chain.",
           20.32, 151.13)
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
